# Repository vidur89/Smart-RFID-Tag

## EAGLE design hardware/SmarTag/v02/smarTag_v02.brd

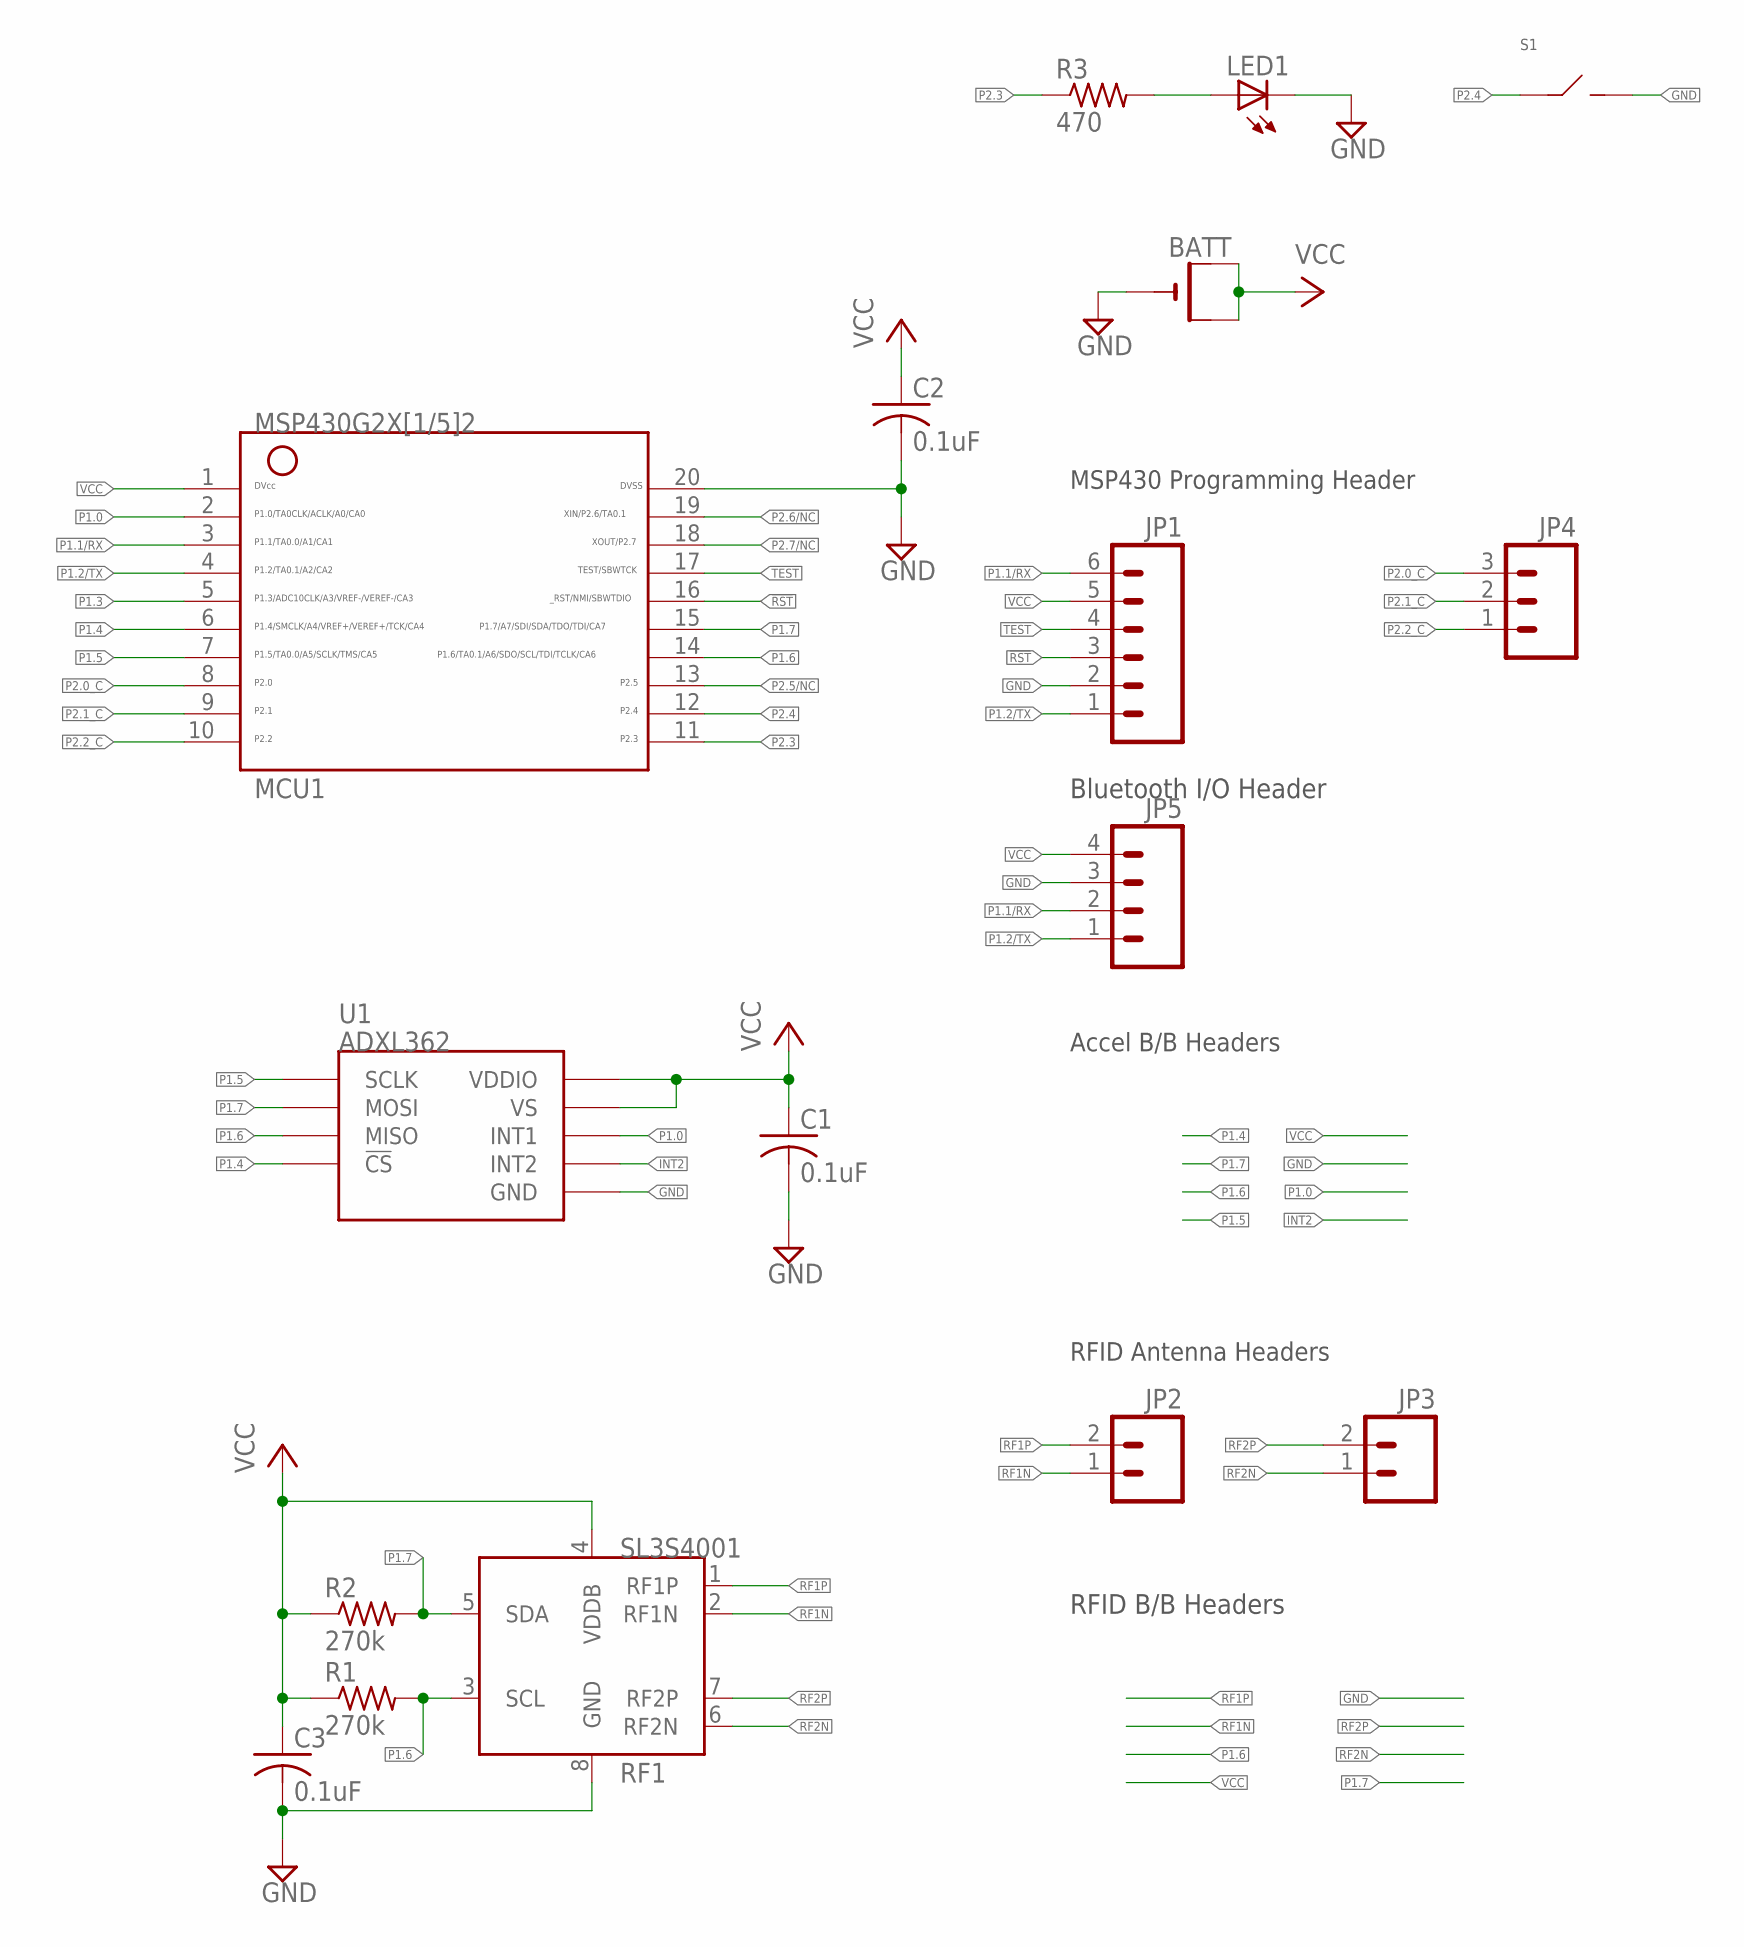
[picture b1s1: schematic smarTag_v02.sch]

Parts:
BATT: CR2032SMT; CR2032-SMD
C1, C3: 0.1uF; C0805
C2: 0.1uF; C0805K
JP1: M061.27MM; 1X06-1.27MM
JP2, JP3: M02LOCK; 1X02_LOCK
JP4: M03LOCK; 1X03_LOCK
JP5: M04LOCK; 1X04_LOCK
LED1: LEDCHIP-LED0805; CHIP-LED0805
MCU1: G2X[1/5]2---PW20; PW20
R1, R2: 270k; R0805
R3: 470; R0805
RF1: SL3S4001; SOT902-1/2/3
S1: SPST_B3FS-1000; B3FS-1000
U1: ADXL362

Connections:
!RST: JP1.3, MCU1.16
GND: BATT.-, C1.2, C2.2, C3.2, JP1.2, JP5.3, LED1.C, MCU1.20, RF1.8 (GND), S1.3 (B), S1.4 (B), U1.P$12 (GND), U1.P$13 (GND), U1.P$16 (GND)
INT2: U1.P$9 (INT2)
unnamed: LED1.A, R3.2
P1.0: MCU1.2, U1.P$11 (INT1)
P1.1/RX: JP1.6, JP5.2, MCU1.3
P1.2/TX: JP1.1, JP5.1, MCU1.4
P1.3: MCU1.5
P1.4: MCU1.6, U1.P$8 (!CS)
P1.5: MCU1.7, U1.P$4 (SCLK)
P1.6: MCU1.14, R1.2, RF1.3 (SCL), U1.P$7 (MISO)
P1.7: MCU1.15, R2.2, RF1.5 (SDA), U1.P$6 (MOSI)
P2.0_C: JP4.3, MCU1.8
P2.1_C: JP4.2, MCU1.9
P2.2_C: JP4.1, MCU1.10
P2.3: MCU1.11, R3.1
P2.4: MCU1.12, S1.1 (A), S1.2 (A)
P2.5/NC: MCU1.13
P2.6/NC: MCU1.19
P2.7/NC: MCU1.18
RF1N: JP2.1, RF1.2 (RF1N)
RF1P: JP2.2, RF1.1 (RF1P)
RF2N: JP3.1, RF1.6 (RF2N)
RF2P: JP3.2, RF1.7 (RF2P)
TEST: JP1.4, MCU1.17
VCC: BATT.+$1 (+), BATT.+$2 (+1), C1.1, C2.1, C3.1, JP1.5, JP5.4, MCU1.1, R1.1, R2.1, RF1.4 (VDDB), U1.P$1 (VDDIO), U1.P$14 (VS)

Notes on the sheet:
MSP430 Programming Header
RFID Antenna Headers
Accel B/B Headers
Bluetooth I/O Header
RFID B/B Headers

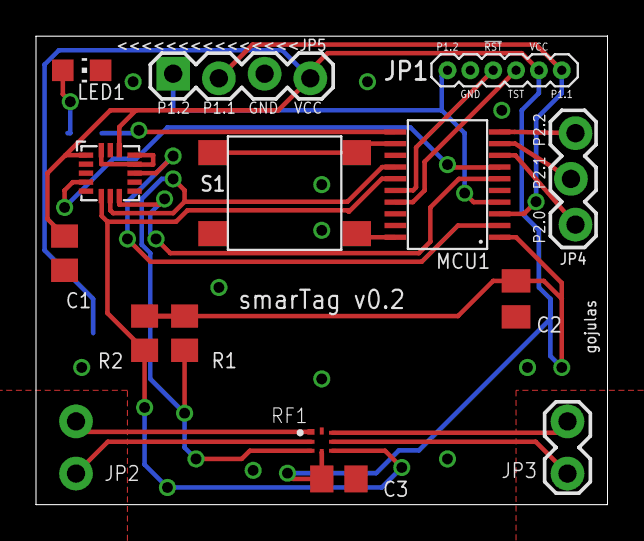
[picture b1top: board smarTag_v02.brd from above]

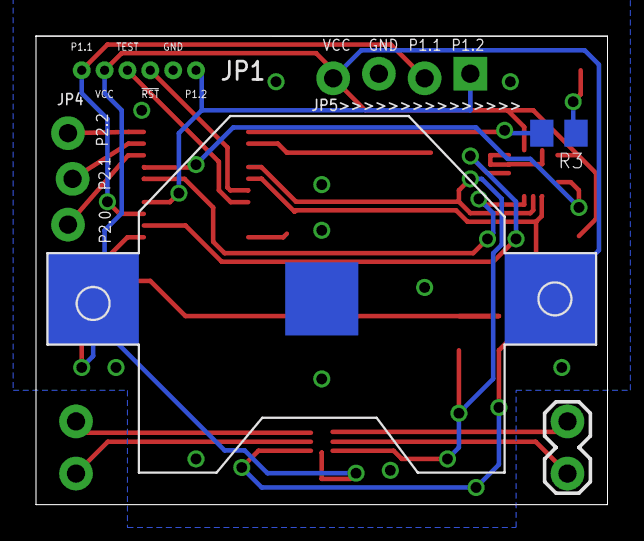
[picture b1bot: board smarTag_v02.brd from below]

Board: 2 copper layers, 31.8 x 26.0 mm, 17 parts (3 on the bottom side), 21 nets.

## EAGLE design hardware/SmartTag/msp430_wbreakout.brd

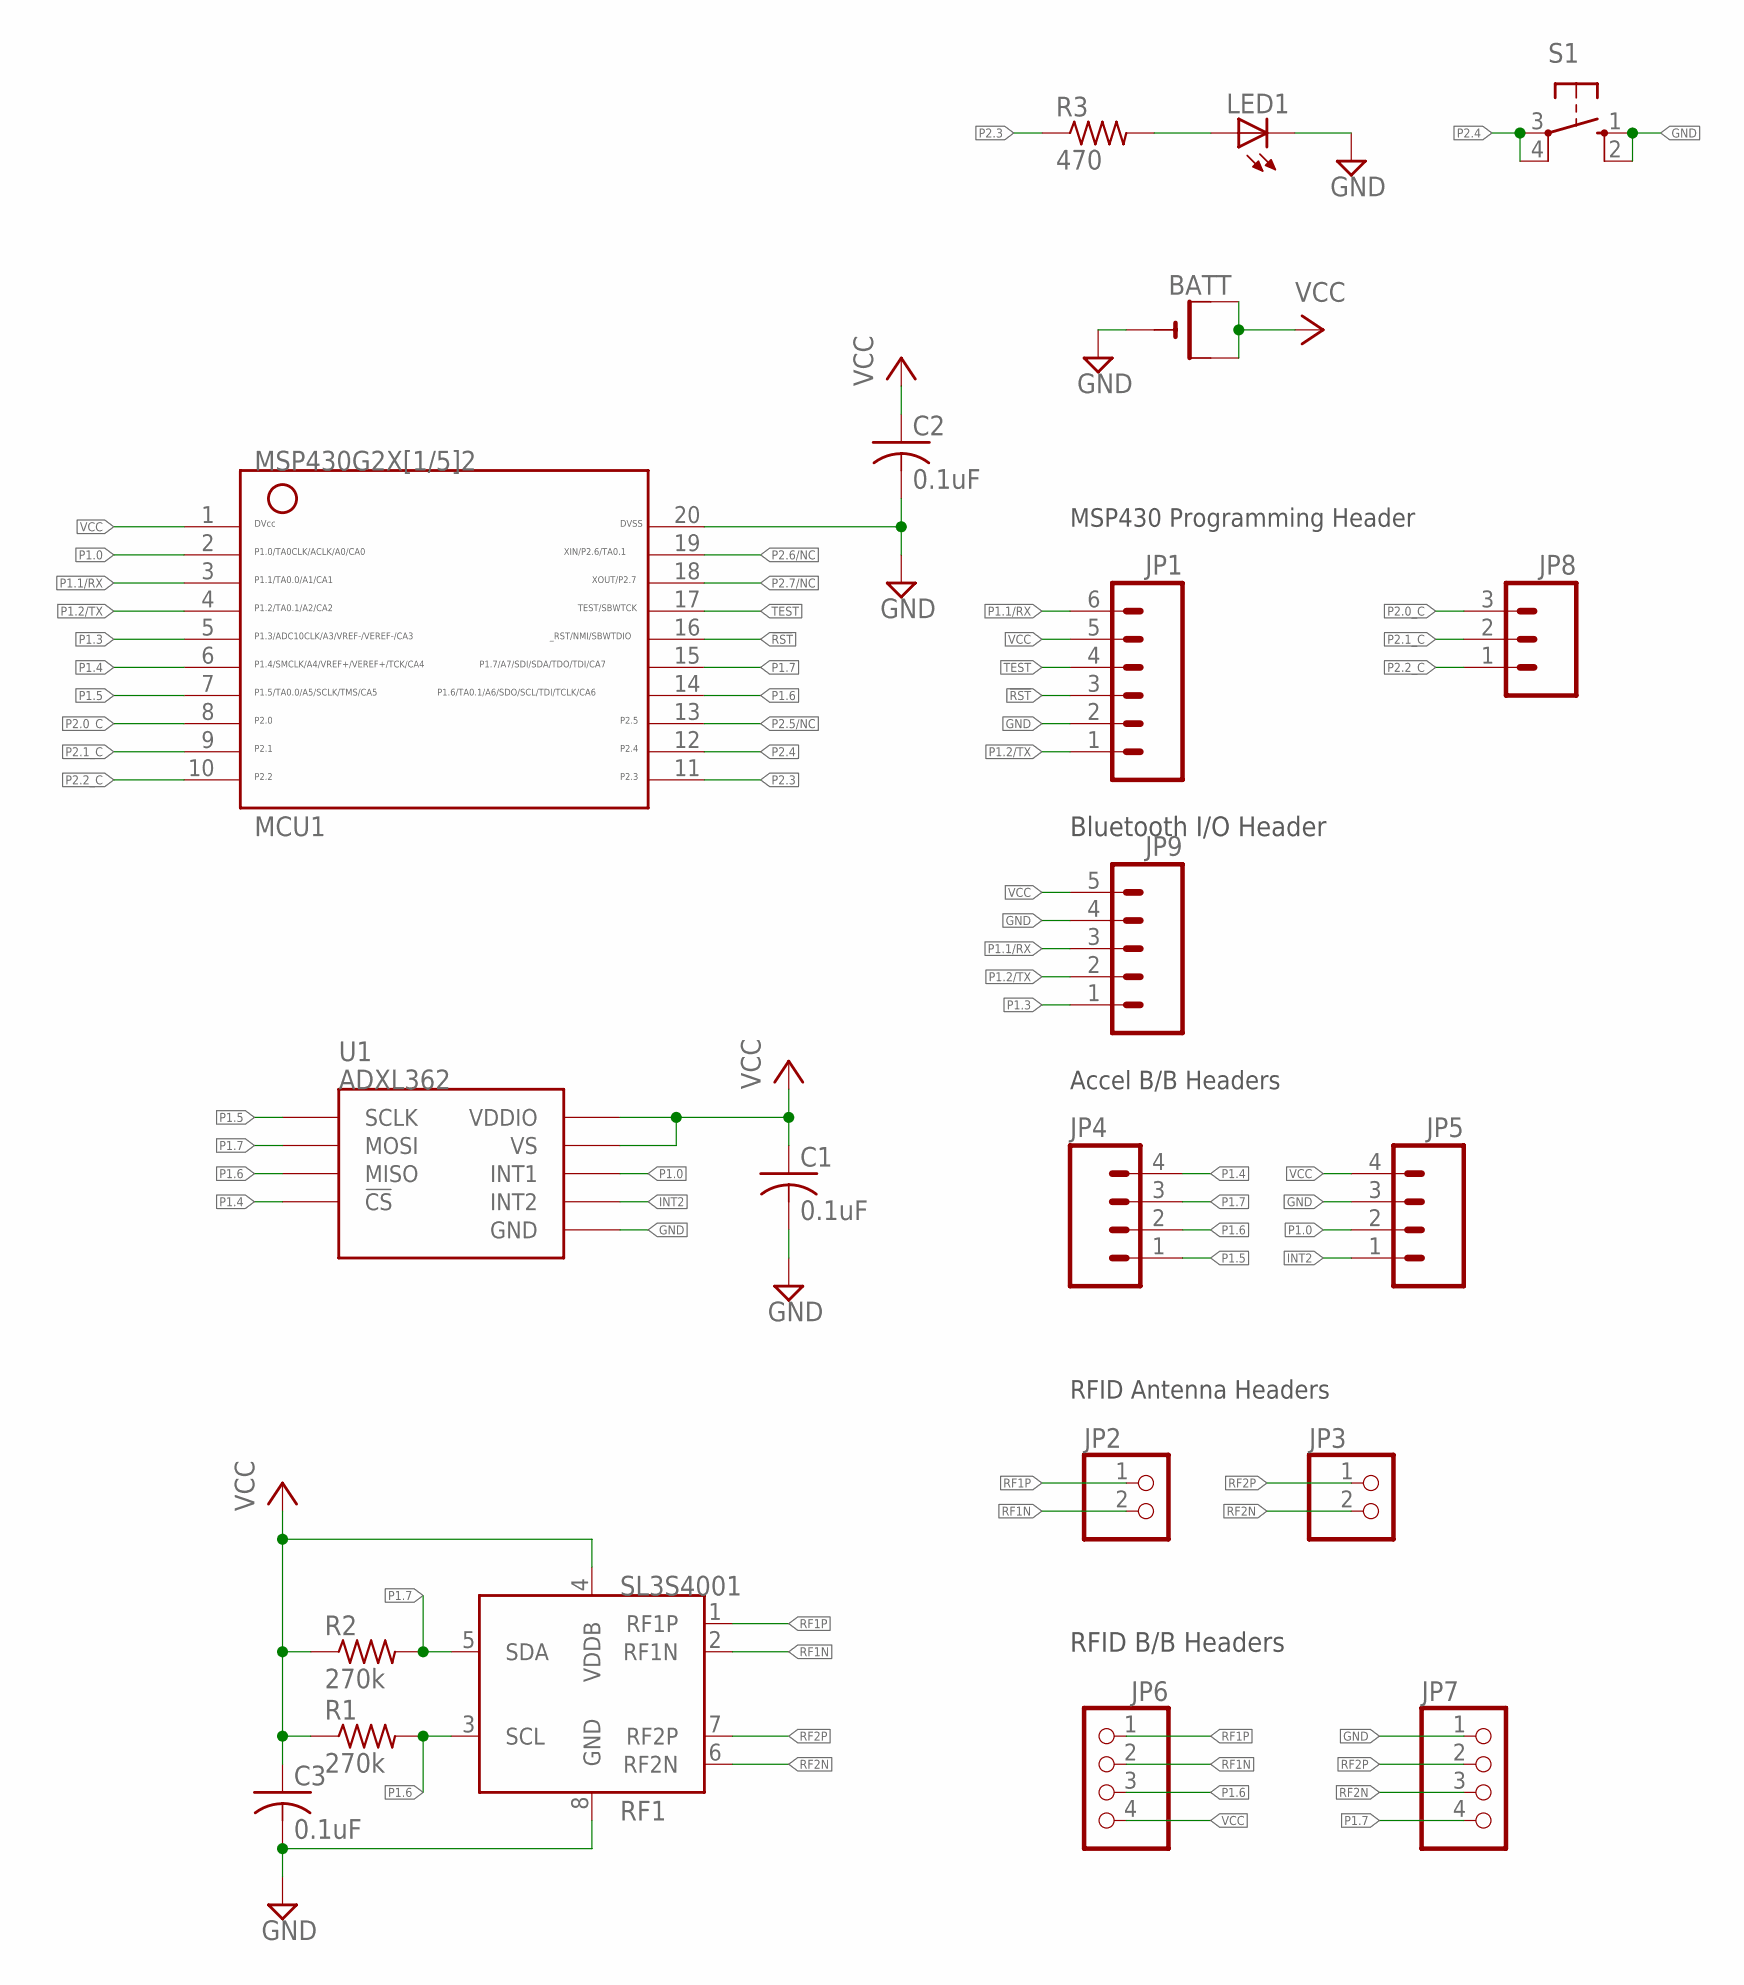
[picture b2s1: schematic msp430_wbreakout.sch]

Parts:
BATT: CR2032SMT; CR2032-SMD
C1, C3: 0.1uF; C0805
C2: 0.1uF; C0805K
JP1: M06LOCK; 1X06_LOCK
JP2, JP3: PINHD-1X2; 1X02
JP4, JP5: M04LOCK; 1X04_LOCK
JP6, JP7: PINHD-1X4; 1X04
JP8: M03LOCK; 1X03_LOCK
JP9: M05LOCK; 1X05_LOCK
LED1: LEDCHIP-LED0805; CHIP-LED0805
MCU1: G2X[1/5]2---PW20; PW20
R1, R2: 270k; R0805
R3: 470; R0805
RF1: SL3S4001; SOT902-1/2/3
S1: 10-XX; B3F-10XX
U1: ADXL362

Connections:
!RST: JP1.3, MCU1.16
DVSS: C2.2, MCU1.20
GND: BATT.-, C1.2, C3.2, JP1.2, JP5.3, JP7.1, JP9.4, LED1.C, RF1.8 (GND), S1.1 (S), S1.2 (S1), U1.P$12 (GND), U1.P$13 (GND), U1.P$16 (GND)
INT2: JP5.1, U1.P$9 (INT2)
unnamed: LED1.A, R3.2
P1.0: JP5.2, MCU1.2, U1.P$11 (INT1)
P1.1/RX: JP1.6, JP9.3, MCU1.3
P1.2/TX: JP1.1, JP9.2, MCU1.4
P1.3: JP9.1, MCU1.5
P1.4: JP4.4, MCU1.6, U1.P$8 (!CS)
P1.5: JP4.1, MCU1.7, U1.P$4 (SCLK)
P1.6: JP4.2, JP6.3, MCU1.14, R1.2, RF1.3 (SCL), U1.P$7 (MISO)
P1.7: JP4.3, JP7.4, MCU1.15, R2.2, RF1.5 (SDA), U1.P$6 (MOSI)
P2.0_C: JP8.3, MCU1.8
P2.1_C: JP8.2, MCU1.9
P2.2_C: JP8.1, MCU1.10
P2.3: MCU1.11, R3.1
P2.4: MCU1.12, S1.3, S1.4 (P1)
P2.5/NC: MCU1.13
P2.6/NC: MCU1.19
P2.7/NC: MCU1.18
RF1N: JP2.2, JP6.2, RF1.2 (RF1N)
RF1P: JP2.1, JP6.1, RF1.1 (RF1P)
RF2N: JP3.2, JP7.3, RF1.6 (RF2N)
RF2P: JP3.1, JP7.2, RF1.7 (RF2P)
TEST: JP1.4, MCU1.17
VCC: BATT.+$1 (+), BATT.+$2 (+1), C1.1, C2.1, C3.1, JP1.5, JP5.4, JP6.4, JP9.5, MCU1.1, R1.1, R2.1, RF1.4 (VDDB), U1.P$1 (VDDIO), U1.P$14 (VS)

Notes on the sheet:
MSP430 Programming Header
RFID Antenna Headers
Accel B/B Headers
Bluetooth I/O Header
RFID B/B Headers

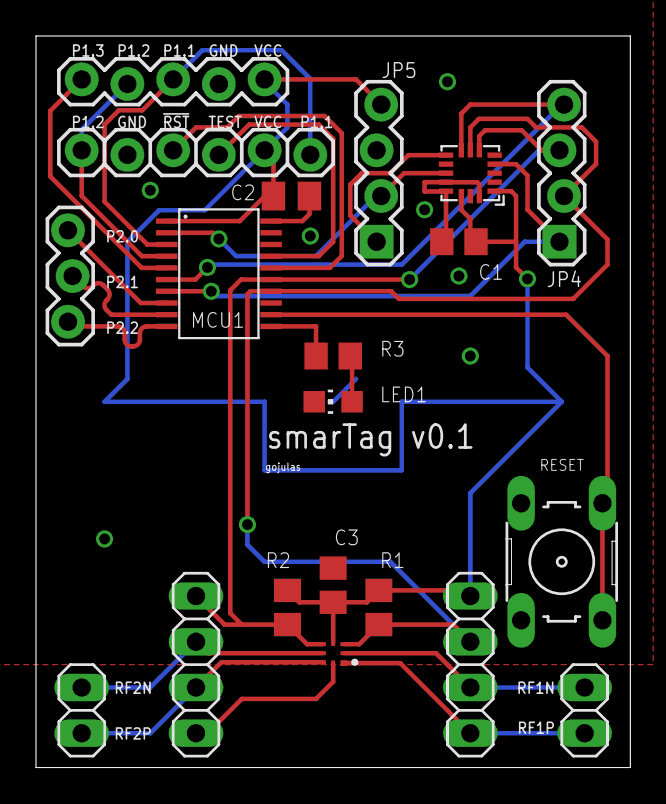
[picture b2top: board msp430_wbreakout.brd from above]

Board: 2 copper layers, 33.0 x 40.6 mm, 21 parts (1 on the bottom side), 24 nets.

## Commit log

2015-08-17 Smart RFID Tag Project Git Repository
    This Repository contains all the code, papers and documentation about
    the SMART RFID TAG. This Repository would also contain a folder
    containing all the referred papers and documents which will help you
    understand the working of the project. Everything is under its proper
    folder.
2015-08-17 Code for the Smart Tag
    17/August/2015
2015-08-17 Create Referred-Material
2015-08-17 ReadMe Information
2015-08-17 not needed
2015-08-19 updated weekly report
2015-08-25 RFID chip replacement options
2015-09-01 ADXL 345 with msp430
    code from https://e2e.ti.com/support/microcontrollers/msp430/f/166/t/260094
2015-09-01 c file
2015-09-01 SPI version for accelerometer
2015-09-15 youngs SPI
2015-09-17 referred material update
2015-09-17 Touch sensor examples
    The folder slac489 has the different capacitive sensor codes. including
    the code for a single button and multiple buttons and slider.
2015-09-22 sep15 findings Power consumption
2015-09-23 new files
2015-09-25 updates for holder and solar cell
2016-01-23 hw: Initial Commit
    Includes 2nd revision of SmartTag board w/ headers for RF and Sensor breakout board
    interconnects.
2016-01-24 hw: Add status LED and capacitive sensor headers
2016-01-26 hw: Add LED to schematic and board.
2016-01-31 hw: Update based on 1/29 Meeting Notes
    Added pin header for Bluetooth board.
    Added RESET switch.
    Rearranged traces for capacitive sensor connections.
    Passed DRC and ERC using SparkFun "Tight" rules
2016-01-31 hw: Rework a few traces.
    Rerouted some traces to remove sharp turns/angles.
    Passed ERC and DRC
2016-02-01 hw: Rework capacitive sensor traces
2016-03-07 hw: Fixed MSP430 DVSS - GND and reorganized files.
2016-03-07 hw: Remove excess backup files, gerbers, etc.
2016-03-07 hw: Add v02 working directory.
    With v02 the goal is miniaturizaiton through the removal of breakout jumper headers.
2016-03-07 hw: Remove JP4-7 from schematic. Add basic board.
2016-03-07 hw: Renumber JP headers and fix BT header.
    Remove P1.3 signal from BT daughter board header.
2016-03-18 hw: Add v02 board.
    A complete rework of the board. Includes a new SMD hard switch, no extraneous breakout board headers, and a much smaller overall profile.
2016-04-05 hw: Move Status LED topside
2016-04-05 hw: Add SmarTag custom parts library
2016-04-05 hw: Add dru rules from SparkFun
2016-04-06 hw: Add updated SparkFun library w/ custom MS06.
2016-04-06 hw: Update board w/ 1.27mm JP1
    This new programming header allows for direct connection with an MSP430
    Launchpad for programming and debugging.
2016-04-20 hw: Add final touches for first production run.
    Add tenting to vias.
    Adjust vias away from battery pads.
    Passed EDC and DRC.
    This version sent to Oshpark on 04-19-2016

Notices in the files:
parts and their libraries:
SparkFun-Connectors: Licensing: Creative Commons ShareAlike 4.0 International - https://creativecommons.org/licenses/by-sa/4.0
NXP_60_26022015: This library may be distributed and adapted freely for any purpose, as long as NXP is credited and any new creation is licensed under the same terms.
